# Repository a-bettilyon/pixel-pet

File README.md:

<br>

⚠️ **Project Status:** Active Development / Work in Progress

<br clear="left">
<br>

<br>

Pixel Pet is a handheld ESP32-S3-based device that brings back the virtual pet experience, built entirely from scratch, including custom PCB, 3D printed enclosure, and original C++ firmware.

The board features a 4-layer custom PCB design (ESP32-S3-WROOM-1, ST7789 TFT display, BMI323 IMU, LiPo charging with power path management, and tactile button input), fabricated and assembled through JLCPCB. The enclosure is designed in Fusion 360 and 3D printed to house the board, display, and battery in a compact handheld form factor.

This project was built as a hands-on portfolio piece to demonstrate end-to-end embedded systems and PCB design skills across schematic capture, layout, firmware development, and mechanical design.

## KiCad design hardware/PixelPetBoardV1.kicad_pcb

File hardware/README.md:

# Hardware

⚠️ **Status:** Active development. PCB currently in bring-up and testing.

KiCad project for the Pixel Pet custom PCB, an ESP32-S3-based board with display, IMU, charging circuit, and user I/O.

## Opening the project

Requires [KiCad](https://www.kicad.org/) (developed in v8). Multiple custom part libraries are used, see  `/libraries`.
## Key design notes

- ESP32-S3-WROOM-1 module, 4-layer board
- BQ24079 LiPo charger with power path management
- BMI323 IMU (SPI), ST7789 TFT display
- Targeting JLCPCB fabrication + SMT assembly, with select hand-soldered THT parts

## Gerbers / BOM freshness

Files in `/gerbers` and `bom.csv` are exported directly from the current `.kicad_pcb`/`.kicad_sch`. If you're building from this repo, pull these rather than any older exports that may exist elsewhere in project history.

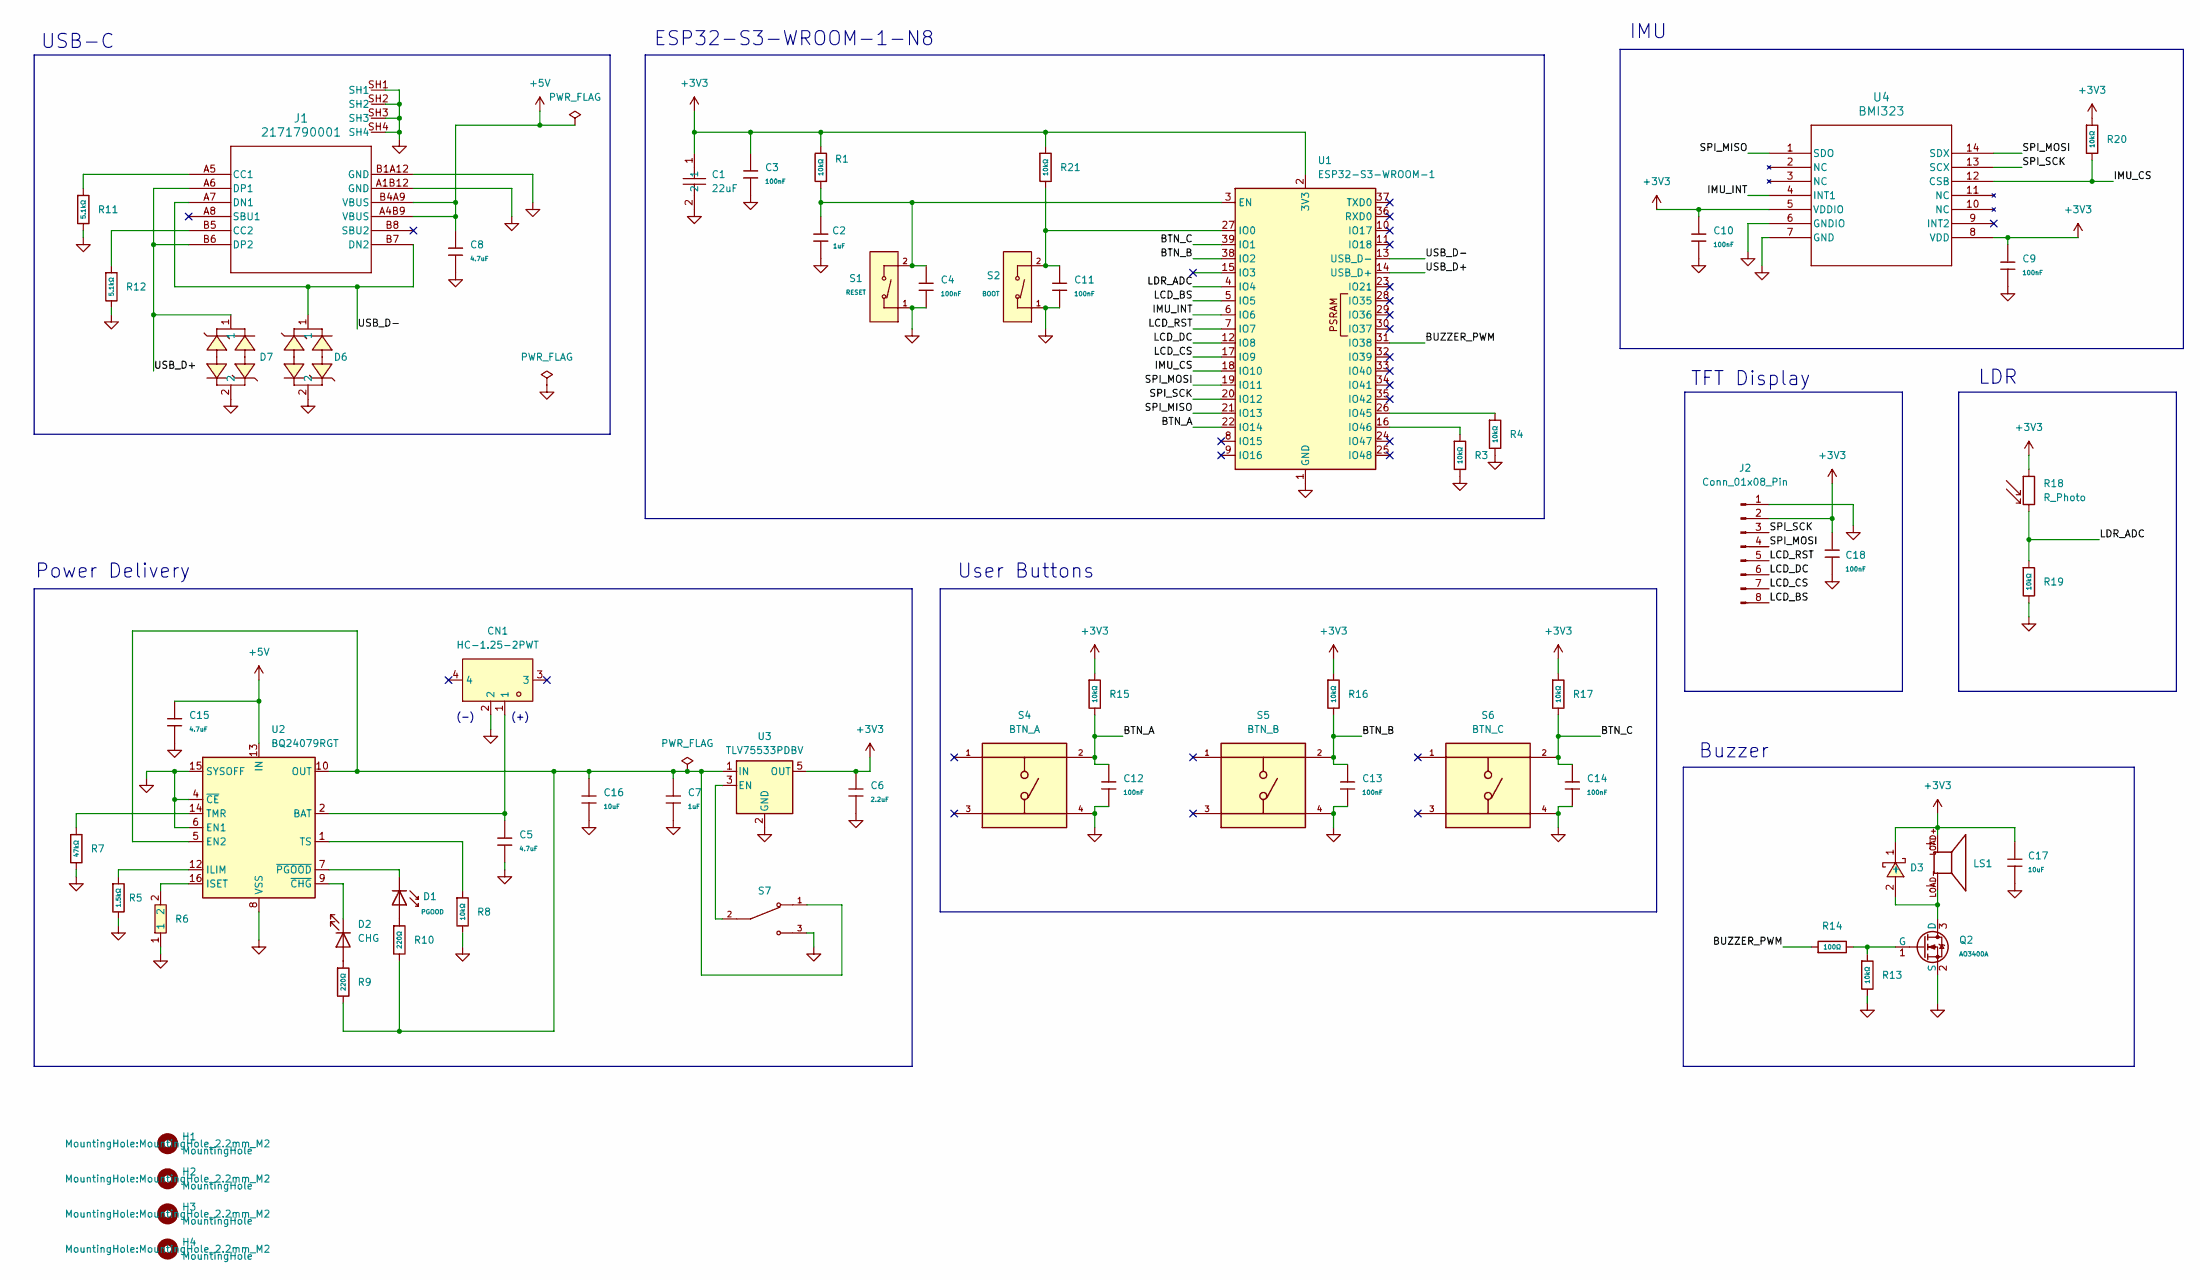
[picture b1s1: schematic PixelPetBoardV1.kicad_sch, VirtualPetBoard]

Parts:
C1: 22uF; C0805; MPN CL21A226MAQNNNE; LCSC Part C45783
C2, C7: 1uF; C_0402; Voltage Rated 25V; Tolerance ±10%; Part CL05A105KA5NQNC; LCSC C52923
C3, C4, C9, C10, C11, C12, C13, C14, C18: 100nF; C_0402; Voltage Rated 16V; Tolerance ±10%; Part CL05B104KO5NNNC; LCSC C1525
C5, C8, C15: 4.7uF; C_0402; Voltage Rated 10V; Tolerance ±20%; Part CL05A475MP5NRNC; LCSC C23733
C6: 2.2uF; C_0603; Voltage Rated 16V; Tolerance ±10%; Part CL10A225KO8NNNC; LCSC C23630
C16, C17: 10uF; C_0603; Voltage Rated 10V; Tolerance ±10%; Part CL10A106KP8NNNC; LCSC C19702
CN1: HC-1.25-2PWT; CONN-SMD_2P-P1.25-HC-1.25-2PWT; MPN HC-1.25-2PWT; LCSC Part C2845379
D1: PGOOD; D_0805; Part KT-0805G; LCSC C2297
D2: CHG; LED_D3.0mm
D3: B5819W_C8598; SOD-123_L2.7-W1.6-LS3.7-RD-1; MPN B5819W SL; LCSC Part C8598
D6, D7: PTVSUC3D5VB; SOD-323_L1.8-W1.3-LS2.5-BI; MPN PTVSUC3D5VB; LCSC Part C918847
H1, H2, H3, H4: MountingHole; MountingHole_2.2mm_M2
J1: 2171790001; 2171790001_MOL
J2: Conn_01x08_Pin; PinHeader_1x08_P2.54mm_Vertical
LS1: SMT-0540-T-9-R; XDCR_SMT-0540-T-9-R; PARTREV A
Q2: AO3400A; Q_SOT-23; Part AO3400A; LCSC C20917
R1: 10kΩ; R_1206; Overload Voltage (Max) 200V; Tolerance ±1%; Part 1206W4F1002T5E; LCSC C17902
R3, R4, R8, R13, R15, R16, R17, R19, R20, R21: 10kΩ; R_0402; Overload Voltage (Max) 50V; Tolerance ±1%; Part 0402WGF1002TCE; LCSC C25744
R5: 1.5kΩ; R_0402; Overload Voltage (Max) 50V; Tolerance ±1%; Part 0402WGF1501TCE; LCSC C25867
R6: 3.9k; R0603; MPN 0603WAF3901T5E; LCSC Part C23018
R7: 47kΩ; R_0402; Overload Voltage (Max) 50V; Tolerance ±1%; Part 0402WGF4702TCE; LCSC C25792
R9, R10: 220Ω; R_0402; Overload Voltage (Max) 50V; Tolerance ±1%; Part 0402WGF2200TCE; LCSC C25091
R11, R12: 5.1kΩ; R_0402; Overload Voltage (Max) 50V; Tolerance ±1%; Part 0402WGF5101TCE; LCSC C25905
R14: 100Ω; R_0402; Overload Voltage (Max) 50V; Tolerance ±1%; Part 0402WGF1000TCE; LCSC C25076
R18: R_Photo; R_LDR_5.1x4.3mm_P3.4mm_Vertical
S1: RESET; SW_TS-1088-AR02016; Voltage Rating (Dc) 12V; Part TS-1088-AR02016; LCSC C720477
S2: BOOT; SW_TS-1088-AR02016; Voltage Rating (Dc) 12V; Part TS-1088-AR02016; LCSC C720477
S4: BTN_A; SW_TS02-66-160-BK-160-LCR-D; PARTREV 1.0
S5: BTN_B; SW_TS02-66-160-BK-160-LCR-D; PARTREV 1.0
S6: BTN_C; SW_TS02-66-160-BK-160-LCR-D; PARTREV 1.0
S7: SLW-864574-5A-RA-N-D; SW_SLW-864574-5A-RA-N-D; PARTREV 1.01
U1: ESP32-S3-WROOM-1; ESP32-S3-WROOM-1-Custom
U2: BQ24079RGT; VQFN-16-1EP_3x3mm_P0.5mm_EP1.6x1.6mm
U3: TLV75533PDBV; SOT-23-5
U4: BMI323; BMI323_BOS

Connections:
+3V3: C1.1, C3.1, C6.1, C9.2, C10.1, C17.1, C18.1, D3.1 (-), J2.2, LS1.LOAD+, R1.2, R15.1, R16.1, R17.1, R18.1, R20.1, R21.1, U1.2 (3V3), U3.5 (OUT), U4.5 (VDDIO), U4.8 (VDD)
+5V: C8.1, C15.1, J1.A4B9 (VBUS), J1.B4A9 (VBUS), U2.13 (IN)
/BTN_A: C12.1, R15.2, S4.2, U1.22 (IO14)
/BTN_B: C13.1, R16.2, S5.2, U1.38 (IO2)
/BTN_C: C14.1, R17.2, S6.2, U1.39 (IO1)
/BUZZER_PWM: R14.1, U1.31 (IO38)
/IMU_CS: R20.2, U1.18 (IO10), U4.12 (CSB)
/IMU_INT: U1.6 (IO6), U4.4 (INT1)
/LCD_BS: J2.8, U1.5 (IO5)
/LCD_CS: J2.7, U1.17 (IO9)
/LCD_DC: J2.6, U1.12 (IO8)
/LCD_RST: J2.5, U1.7 (IO7)
/LDR_ADC: R18.2, R19.1, U1.4 (IO4)
/SPI_MISO: U1.21 (IO13), U4.1 (SDO)
/SPI_MOSI: J2.4, U1.19 (IO11), U4.14 (SDX)
/SPI_SCK: J2.3, U1.20 (IO12), U4.13 (SCX)
/USB_D+: D7.1, J1.A6 (DP1), J1.B6 (DP2), U1.14 (USB_D+)
/USB_D-: D6.1, J1.A7 (DN1), J1.B7 (DN2), U1.13 (USB_D-)
GND: C1.2, C2.1, C3.2, C4.2, C5.2, C6.2, C7.2, C8.2, C9.1, C10.2, C11.2, C12.2, C13.2, C14.2, C15.2, C16.2, C17.2, C18.2, CN1.2, D6.2, D7.2, J1.A1B12 (GND), J1.B1A12 (GND), J1.SH1, J1.SH2, J1.SH3, J1.SH4, J2.1, Q2.2 (S), R3.2, R4.2, R5.2, R6.1, R7.2, R8.2, R11.2, R12.2, R13.2, R19.2, S1.1 (A), S2.1 (A), S4.4, S5.4, S6.4, S7.3, U1.1 (GND), U1.40 (GND), U1.41 (GND), U2.4 (~CE), U2.6 (EN1), U2.8 (VSS), U2.15 (SYSOFF), U2.17 (VSS), U3.2 (GND), U4.6 (GNDIO), U4.7 (GND)
unnamed: C5.1, CN1.1, U2.2 (BAT), U2.3 (BAT)
unnamed: D1.2, R10.1
unnamed: D2.2 (A), R9.1
unnamed: D2.1 (K), U2.9 (~CHG)
unnamed: D3.2 (+), LS1.LOAD-, Q2.3 (D)
unnamed: J1.A5 (CC1), R11.1
unnamed: J1.B5 (CC2), R12.1
unnamed: Q2.1 (G), R13.1, R14.2
unnamed: C2.2, C4.1, R1.1, S1.2 (B), U1.3 (EN)
unnamed: C11.1, R21.2, S2.2 (B), U1.27 (IO0)
unnamed: R4.1, U1.26 (IO45)
unnamed: R3.1, U1.16 (IO46)
unnamed: C7.1, C16.1, R9.2, R10.2, S7.1, U2.5 (EN2), U2.10 (OUT), U2.11 (OUT), U3.1 (IN)
unnamed: R5.1, U2.12 (ILIM)
unnamed: R6.2, U2.16 (ISET)
unnamed: R7.1, U2.14 (TMR)
unnamed: R8.1, U2.1 (TS)
unnamed: D1.1, U2.7 (~PGOOD)
unnamed: S7.2, U3.3 (EN)

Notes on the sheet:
Buzzer
ESP32-S3-WROOM-1-N8
(+)
LDR
IMU
(-)
TFT Display
User Buttons
USB-C
Power Delivery

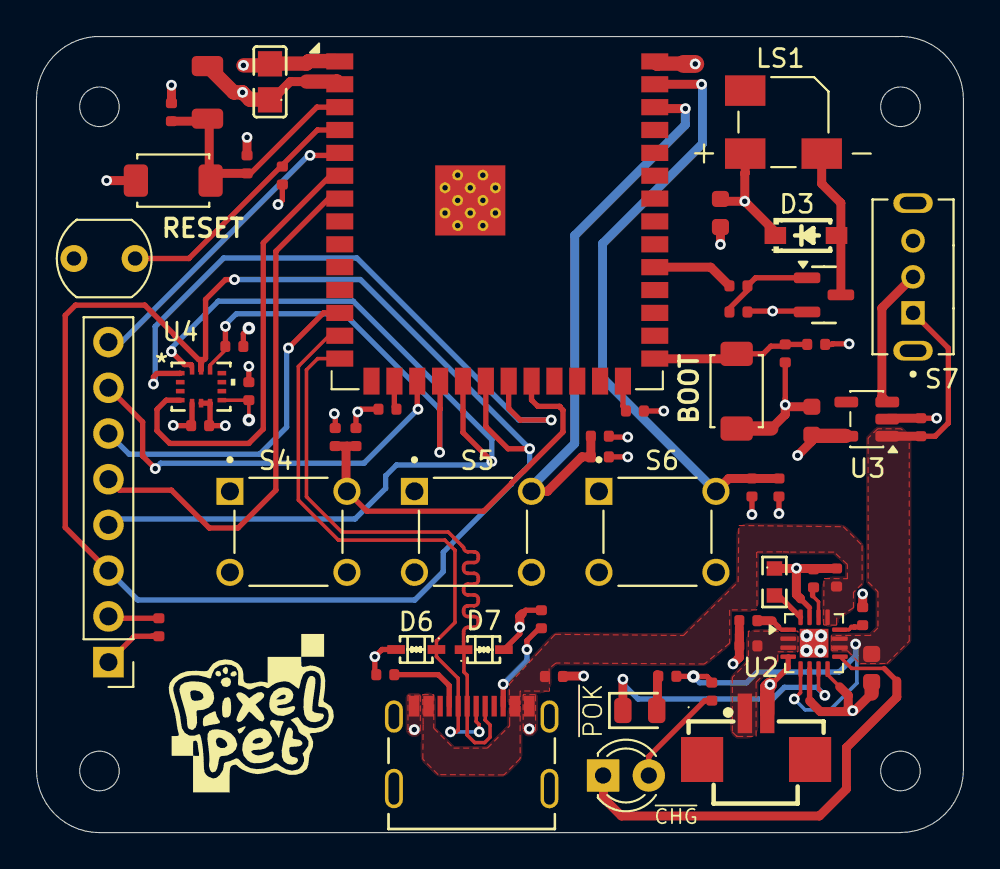
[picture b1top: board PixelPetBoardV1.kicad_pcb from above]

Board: 4 copper layers, 51.5 x 44.2 mm, 62 parts (0 on the bottom side), 38 nets.

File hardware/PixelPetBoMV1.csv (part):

,Status,Reference,Value,Footprint,LCSC,Part,Manufacturer,Description,Datasheet/Listing
1,Basic,C1,22uF,C0805,C45783,CL21A226MAQNNNE,SAMSUNG(三星),,https://lcsc.com/product-detail/Multilayer-Ceramic-Capacitor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
2,Basic,C2,1uF,C_0402,C52923,CL05A105KA5NQNC,Samsung Electro-Mechanics,25V 1uF X5R ±10% 0402 Multilayer Ceramic Capacitors MLCC - SMD/SMT ROHS,https://www.lcsc.com/datasheet/lcsc_datasheet_2304140030_Sam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
3,Basic,C3,100nF,C_0402,C1525,CL05B104KO5NNNC,Samsung Electro-Mechanics,16V 100nF X7R ±10% 0402 Multilayer Ceramic Capacitors MLCC - SMD/SMT ROHS,https://www.lcsc.com/datasheet/lcsc_datasheet_2304140030_Sam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
4,Basic,C4,100nF,C_0402,C1525,CL05B104KO5NNNC,Samsung Electro-Mechanics,16V 100nF X7R ±10% 0402 Multilayer Ceramic Capacitors MLCC - SMD/SMT ROHS,https://www.lcsc.com/datasheet/lcsc_datasheet_2304140030_Sam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
5,Basic,C5,4.7uF,C_0402,C23733,CL05A475MP5NRNC,Samsung Electro-Mechanics,10V 4.7uF X5R ±20% 0402 Multilayer Ceramic Capacitors MLCC - SMD/SMT ROHS,https://www.lcsc.com/datasheet/lcsc_datasheet_2304140030_Sam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
6,Basic,C6,2.2uF,C_0603,C23630,CL10A225KO8NNNC,Samsung Electro-Mechanics,16V 2.2uF X5R ±10% 0603 Multilayer Ceramic Capacitors MLCC - SMD/SMT ROHS,https://www.lcsc.com/datasheet/lcsc_datasheet_2304140030_Sam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
7,Basic,C7,1uF,C_0402,C52923,CL05A105KA5NQNC,Samsung Electro-Mechanics,25V 1uF X5R ±10% 0402 Multilayer Ceramic Capacitors MLCC - SMD/SMT ROHS,https://www.lcsc.com/datasheet/lcsc_datasheet_2304140030_Sam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
8,Basic,C8,4.7uF,C_0402,C23733,CL05A475MP5NRNC,Samsung Electro-Mechanics,10V 4.7uF X5R ±20% 0402 Multilayer Ceramic Capacitors MLCC - SMD/SMT ROHS,https://www.lcsc.com/datasheet/lcsc_datasheet_2304140030_Sam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
9,Basic,C9,100nF,C_0402,C1525,CL05B104KO5NNNC,Samsung Electro-Mechanics,16V 100nF X7R ±10% 0402 Multilayer Ceramic Capacitors MLCC - SMD/SMT ROHS,https://www.lcsc.com/datasheet/lcsc_datasheet_2304140030_Sam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
10,Basic,C10,100nF,C_0402,C1525,CL05B104KO5NNNC,Samsung Electro-Mechanics,16V 100nF X7R ±10% 0402 Multilayer Ceramic Capacitors MLCC - SMD/SMT ROHS,https://www.lcsc.com/datasheet/lcsc_datasheet_2304140030_Sam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
11,Basic,C11,100nF,C_0402,C1525,CL05B104KO5NNNC,Samsung Electro-Mechanics,16V 100nF X7R ±10% 0402 Multilayer Ceramic Capacitors MLCC - SMD/SMT ROHS,https://www.lcsc.com/datasheet/lcsc_datasheet_2304140030_Sam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
12,Basic,C12,100nF,C_0402,C1525,CL05B104KO5NNNC,Samsung Electro-Mechanics,16V 100nF X7R ±10% 0402 Multilayer Ceramic Capacitors MLCC - SMD/SMT ROHS,https://www.lcsc.com/datasheet/lcsc_datasheet_2304140030_Sam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
13,Basic,C13,100nF,C_0402,C1525,CL05B104KO5NNNC,Samsung Electro-Mechanics,16V 100nF X7R ±10% 0402 Multilayer Ceramic Capacitors MLCC - SMD/SMT ROHS,https://www.lcsc.com/datasheet/lcsc_datasheet_2304140030_Sam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
14,Basic,C14,100nF,C_0402,C1525,CL05B104KO5NNNC,Samsung Electro-Mechanics,16V 100nF X7R ±10% 0402 Multilayer Ceramic Capacitors MLCC - SMD/SMT ROHS,https://www.lcsc.com/datasheet/lcsc_datasheet_2304140030_Sam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
15,Basic,C15,4.7uF,C_0402,C23733,CL05A475MP5NRNC,Samsung Electro-Mechanics,10V 4.7uF X5R ±20% 0402 Multilayer Ceramic Capacitors MLCC - SMD/SMT ROHS,https://www.lcsc.com/datasheet/lcsc_datasheet_2304140030_Sam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
16,Basic,C16,10uF,C_0603,C19702,CL10A106KP8NNNC,Samsung Electro-Mechanics,10V 10uF X5R ±10% 0603 Multilayer Ceramic Capacitors MLCC - SMD/SMT ROHS,https://www.lcsc.com/datasheet/lcsc_datasheet_2304140030_Sam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
17,Basic,C17,10uF,C_0603,C19702,CL10A106KP8NNNC,Samsung Electro-Mechanics,10V 10uF X5R ±10% 0603 Multilayer Ceramic Capacitors MLCC - SMD/SMT ROHS,https://www.lcsc.com/datasheet/lcsc_datasheet_2304140030_Sam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
18,Basic,C18,100nF,C_0402,C1525,CL05B104KO5NNNC,Samsung Electro-Mechanics,16V 100nF X7R ±10% 0402 Multilayer Ceramic Capacitors MLCC - SMD/SMT ROHS,https://www.lcsc.com/datasheet/lcsc_datasheet_2304140030_Sam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
19,Basic,R1,10kΩ,R_1206,C17902,1206W4F1002T5E,UNI-ROYAL(Uniroyal Elec),250mW Thick Film Resistors 200V ±100ppm/°C ±1% 10kΩ 1206 Chip Resistor - Surface Mount ROHS,https://www.lcsc.com/datasheet/lcsc_datasheet_2206010145_UNI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
20,Basic,R3,10kΩ,R_0402,C25744,0402WGF1002TCE,UNI-ROYAL(Uniroyal Elec),62.5mW Thick Film Resistors 50V ±100ppm/°C ±1% 10kΩ 0402 Chip Resistor - Surface Mount ROHS,https://www.lcsc.com/datasheet/lcsc_datasheet_2411221126_UNI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
21,Basic,R4,10kΩ,R_0402,C25744,0402WGF1002TCE,UNI-ROYAL(Uniroyal Elec),62.5mW Thick Film Resistors 50V ±100ppm/°C ±1% 10kΩ 0402 Chip Resistor - Surface Mount ROHS,https://www.lcsc.com/datasheet/lcsc_datasheet_2411221126_UNI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
22,Basic,R5,1.5kΩ,R_0402,C25867,0402WGF1501TCE,UNI-ROYAL(Uniroyal Elec),62.5mW Thick Film Resistors 50V ±100ppm/°C ±1% 1.5kΩ 0402 Chip Resistor - Surface Mount ROHS,https://www.lcsc.com/datasheet/lcsc_datasheet_2206010045_UNI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
23,Basic,R6,3.9k,R0603,C23018,0603WAF3901T5E,UNI-ROYAL(厚声),3.9KΩ (3901) ±1%,https://lcsc.com/product-detail/Chip-Resistor-Surface-Mount-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
24,Basic,R7,47kΩ,R_0402,C25792,0402WGF4702TCE,UNI-ROYAL(Uniroyal Elec),62.5mW Thick Film Resistors 50V ±100ppm/°C ±1% 47kΩ 0402 Chip Resistor - Surface Mount ROHS,https://www.lcsc.com/datasheet/lcsc_datasheet_2206010100_UNI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
25,Basic,R8,10kΩ,R_0402,C25744,0402WGF1002TCE,UNI-ROYAL(Uniroyal Elec),62.5mW Thick Film Resistors 50V ±100ppm/°C ±1% 10kΩ 0402 Chip Resistor - Surface Mount ROHS,https://www.lcsc.com/datasheet/lcsc_datasheet_2411221126_UNI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
26,Basic,R9,220Ω,R_0402,C25091,0402WGF2200TCE,UNI-ROYAL(Uniroyal Elec),62.5mW Thick Film Resistors 50V ±100ppm/°C ±1% 220Ω 0402 Chip Resistor - Surface Mount ROHS,https://www.lcsc.com/datasheet/lcsc_datasheet_2205311900_UNI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
27,Basic,R10,220Ω,R_0402,C25091,0402WGF2200TCE,UNI-ROYAL(Uniroyal Elec),62.5mW Thick Film Resistors 50V ±100ppm/°C ±1% 220Ω 0402 Chip Resistor - Surface Mount ROHS,https://www.lcsc.com/datasheet/lcsc_datasheet_2205311900_UNI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
28,Basic,R11,5.1kΩ,R_0402,C25905,0402WGF5101TCE,UNI-ROYAL(Uniroyal Elec),62.5mW Thick Film Resistors 50V ±100ppm/°C ±1% 5.1kΩ 0402 Chip Resistor - Surface Mount ROHS,https://www.lcsc.com/datasheet/lcsc_datasheet_2206010045_UNI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
29,Basic,R12,5.1kΩ,R_0402,C25905,0402WGF5101TCE,UNI-ROYAL(Uniroyal Elec),62.5mW Thick Film Resistors 50V ±100ppm/°C ±1% 5.1kΩ 0402 Chip Resistor - Surface Mount ROHS,https://www.lcsc.com/datasheet/lcsc_datasheet_2206010045_UNI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
30,Basic,R13,10kΩ,R_0402,C25744,0402WGF1002TCE,UNI-ROYAL(Uniroyal Elec),62.5mW Thick Film Resistors 50V ±100ppm/°C ±1% 10kΩ 0402 Chip Resistor - Surface Mount ROHS,https://www.lcsc.com/datasheet/lcsc_datasheet_2411221126_UNI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
31,Basic,R14,100Ω,R_0402,C25076,0402WGF1000TCE,UNI-ROYAL(Uniroyal Elec),62.5mW Thick Film Resistors 50V ±1% ±200ppm/°C 100Ω 0402 Chip Resistor - Surface Mount ROHS,https://www.lcsc.com/datasheet/lcsc_datasheet_2205311900_UNI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
32,Basic,R15,10kΩ,R_0402,C25744,0402WGF1002TCE,UNI-ROYAL(Uniroyal Elec),62.5mW Thick Film Resistors 50V ±100ppm/°C ±1% 10kΩ 0402 Chip Resistor - Surface Mount ROHS,https://www.lcsc.com/datasheet/lcsc_datasheet_2411221126_UNI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
33,Basic,R16,10kΩ,R_0402,C25744,0402WGF1002TCE,UNI-ROYAL(Uniroyal Elec),62.5mW Thick Film Resistors 50V ±100ppm/°C ±1% 10kΩ 0402 Chip Resistor - Surface Mount ROHS,https://www.lcsc.com/datasheet/lcsc_datasheet_2411221126_UNI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
34,Basic,R17,10kΩ,R_0402,C25744,0402WGF1002TCE,UNI-ROYAL(Uniroyal Elec),62.5mW Thick Film Resistors 50V ±100ppm/°C ±1% 10kΩ 0402 Chip Resistor - Surface Mount ROHS,https://www.lcsc.com/datasheet/lcsc_datasheet_2411221126_UNI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
35,Basic,R18,R_Photo,R_LDR_5.1x4.3mm_P3.4mm_Vertical,,,,Photoresistor,
36,Basic,R19,10kΩ,R_0402,C25744,0402WGF1002TCE,UNI-ROYAL(Uniroyal Elec),62.5mW Thick Film Resistors 50V ±100ppm/°C ±1% 10kΩ 0402 Chip Resistor - Surface Mount ROHS,https://www.lcsc.com/datasheet/lcsc_datasheet_2411221126_UNI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
37,Basic,R20,10kΩ,R_0402,C25744,0402WGF1002TCE,UNI-ROYAL(Uniroyal Elec),62.5mW Thick Film Resistors 50V ±100ppm/°C ±1% 10kΩ 0402 Chip Resistor - Surface Mount ROHS,https://www.lcsc.com/datasheet/lcsc_datasheet_2411221126_UNI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

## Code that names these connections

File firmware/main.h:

#pragma once

#include <SPI.h>
#include <7Semi_BMI323.h>

//pin assignments
const int SPI_MOSI = 11;
const int SPI_MISO = 13;
const int SPI_SCK = 20;

const int IMU_CS = 10;

const int LDR_ADC = 4;

const int BUZZ_PWM_PIN = 31;

const int BTN_A_PIN = 14;
const int BTN_B_PIN = 2;
const int BTN_C_PIN = 1;

const int BTN_RESET_PIN = 3;
const int BTN_BOOT_PIN = 0;

BMI323_7Semi imu;

unsigned long now;

//imu measurements
unsigned long lastIMU = 0;
int delayIMU = 300;
int calibDelayIMU = 2000;
float ax, ay, az;
float gx, gy, gz;

//LDR measurements
unsigned long lastLDR = 0;
int delayLDR = 500;
int rawVolts;
int voltsPercent;

//button values
bool btnBoot;

bool btnAraw;
bool btnBraw;
bool btnCraw;
bool btnA;
bool btnB;
bool btnC;
int btnDebounce = 50;
int btnLongPress = 100;
